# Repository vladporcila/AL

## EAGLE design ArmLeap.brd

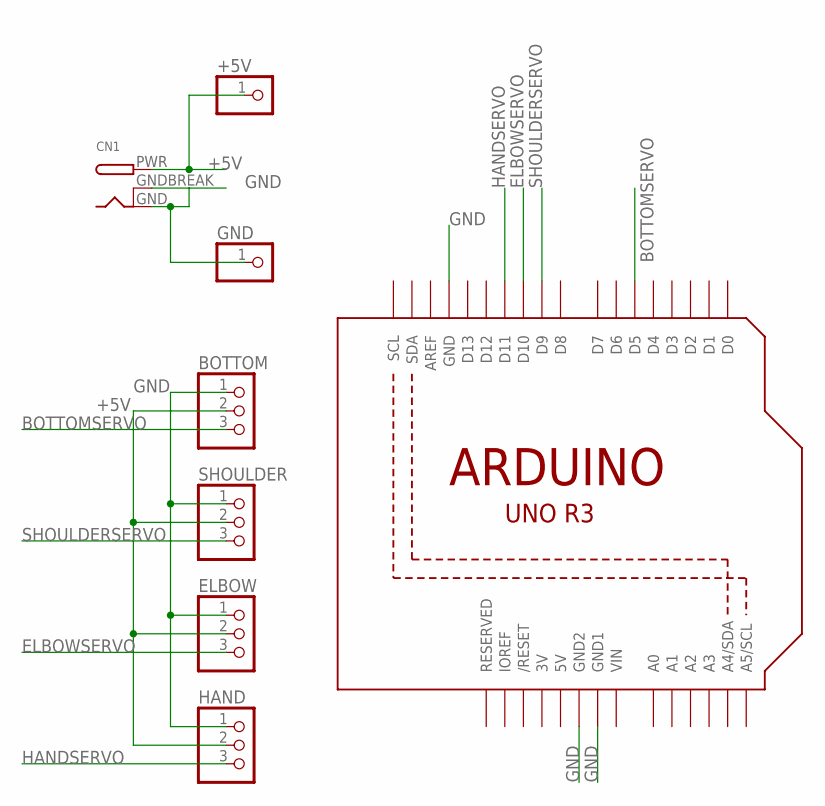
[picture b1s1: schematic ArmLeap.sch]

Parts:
+5V: PINHD-1X1; 1X01
BOTTOM: PINHD-1X3; 1X03
CN1: DCBARRELPTH; DCJACK_2MM_PTH
ELBOW: PINHD-1X3; 1X03
GND: PINHD-1X1; 1X01
HAND: PINHD-1X3; 1X03
SHOULDER: PINHD-1X3; 1X03
U1: ARDUINOR3-DIMENSION; ARDUINOR3

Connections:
3V: U1.3V
5V: U1.5V
+5V: +5V.1, BOTTOM.2, CN1.PWR, ELBOW.2, HAND.2, SHOULDER.2
BOTTOMSERVO: BOTTOM.3, U1.D5
ELBOWSERVO: ELBOW.3, U1.D10
GND: BOTTOM.1, CN1.GND, CN1.GNDBREAK, ELBOW.1, GND.1, HAND.1, SHOULDER.1, U1.GND, U1.GND1, U1.GND2
HANDSERVO: HAND.3, U1.D11
SHOULDERSERVO: SHOULDER.3, U1.D9
VIN: U1.VIN

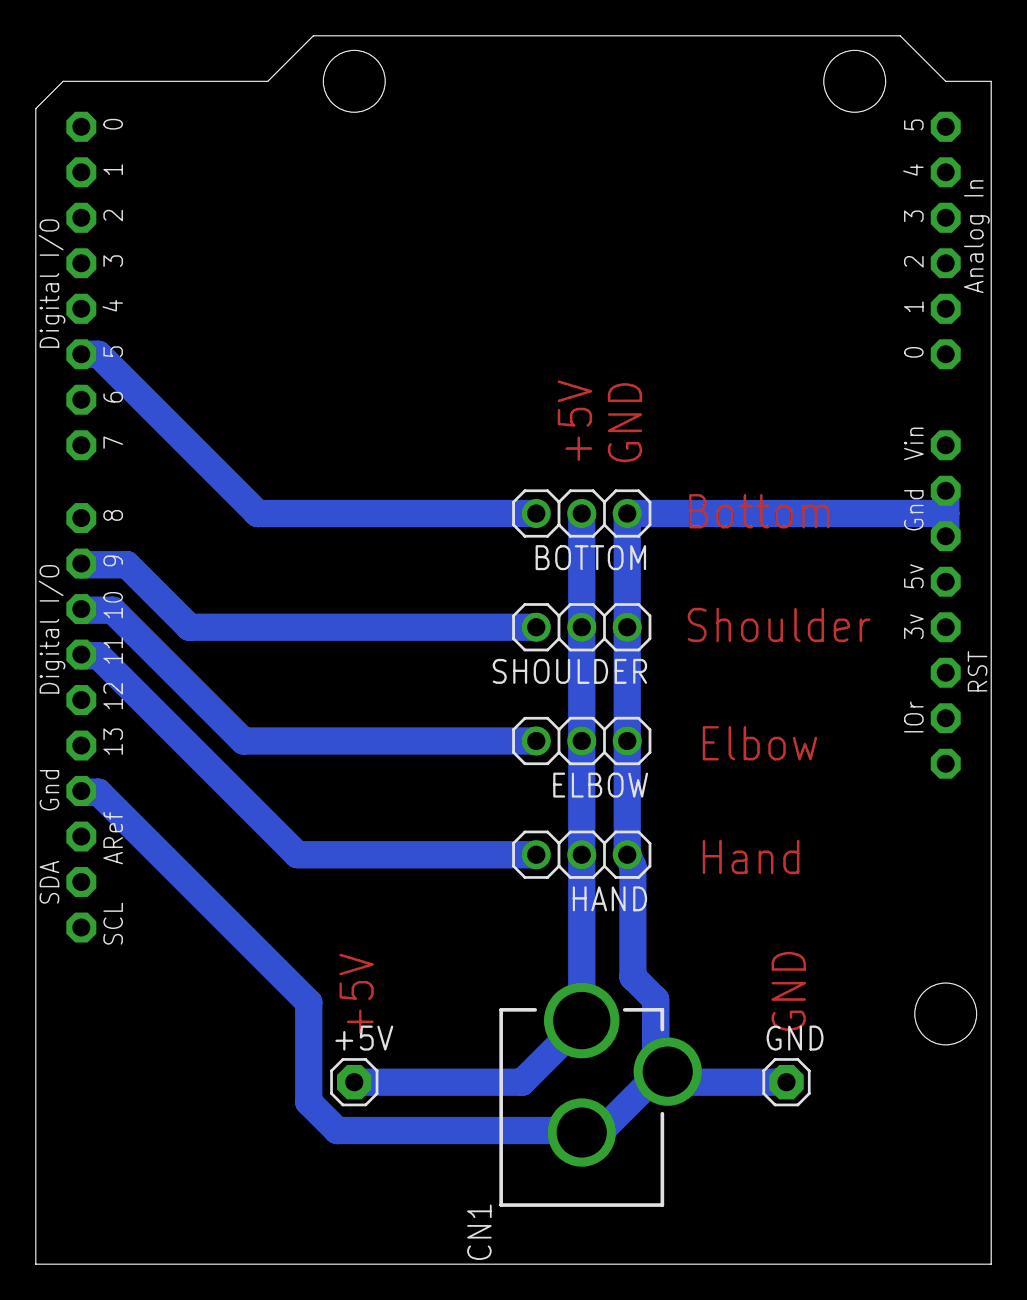
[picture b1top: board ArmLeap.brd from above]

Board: 2 copper layers, 53.3 x 68.6 mm, 8 parts (0 on the bottom side), 6 nets.

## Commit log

2016-10-03 :boom::camel: Added .gitattributes & .gitignore files
2016-10-03 ArmLeap Files
    Careful, the file path is quite large, extract it to the desktop, or in
    C:/AL
2016-10-03 Readme
    Readme
2016-10-03 Board
    Board
